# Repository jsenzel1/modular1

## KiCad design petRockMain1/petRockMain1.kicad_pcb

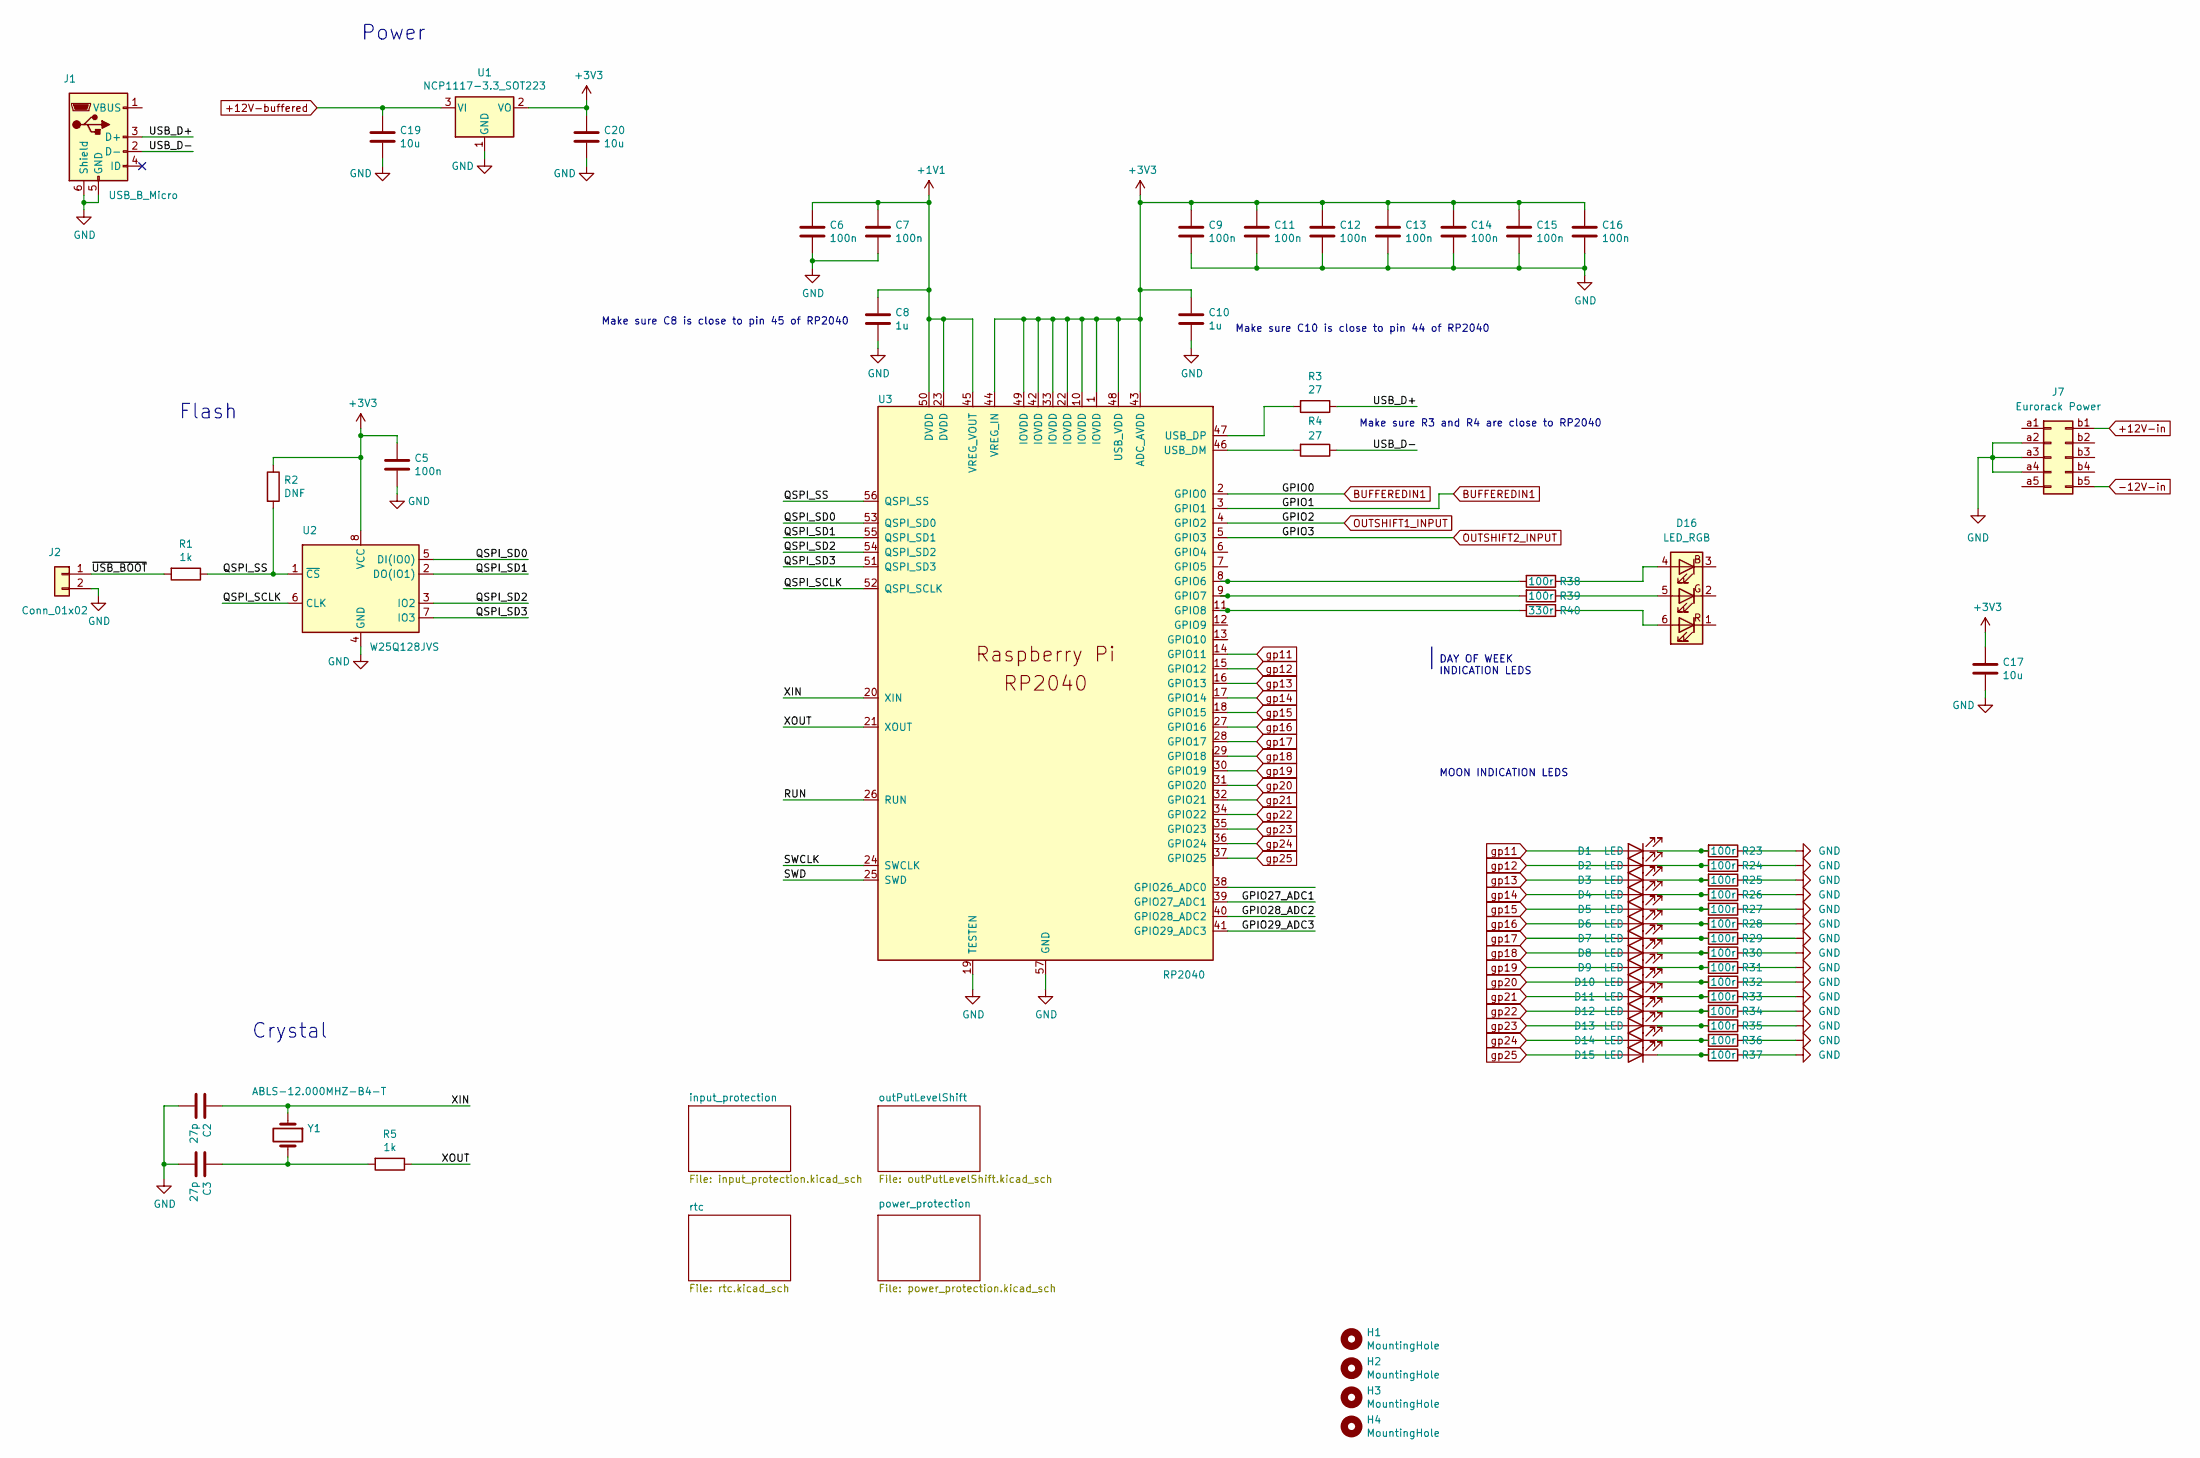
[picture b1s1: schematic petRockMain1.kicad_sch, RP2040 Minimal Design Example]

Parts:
C2, C3: 27p; C_0402_1005Metric
C5, C6, C7, C9, C11, C12, C13, C14, C15, C16: 100n; C_0402_1005Metric
C8, C10: 1u; C_0402_1005Metric
C17, C19, C20: 10u; C_0805_2012Metric
D1, D2, D3, D4, D5, D6, D7, D8, D9, D10, D11, D12, D13, D14, D15: LED; C_0603_1608Metric
D16: LED_RGB; LED_RGB_5050-6
H1, H2, H3, H4: MountingHole; MountingHole_2.7mm_M2.5
J1: USB_B_Micro; USB_Micro-B_Amphenol_10103594-0001LF_Horizontal_modified
J2: Conn_01x02; PinHeader_1x02_P2.54mm_Vertical
J7: Eurorack Power; PinHeader_2x05_P1.00mm_Vertical
R1, R5: 1k; C_0402_1005Metric
R2: DNF; C_0402_1005Metric
R3, R4: 27; C_0402_1005Metric
R23, R24, R25, R26, R27, R28, R29, R30, R31, R32, R33, R34, R35, R36, R37, R38, R39: 100r; C_0402_1005Metric
R40: 330r; C_0402_1005Metric
U1: NCP1117-3.3_SOT223; SOT-223-3_TabPin2
U2: W25Q128JVS; SOIC-8_5.23x5.23mm_P1.27mm
U3: RP2040; RP2040-QFN-56
Y1: ABLS-12.000MHZ-B4-T; Crystal_SMD_HC49-US

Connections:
+1V1: C6.1, C7.1, C8.1, U3.23 (DVDD), U3.45 (VREG_VOUT), U3.50 (DVDD)
+3V3: C5.1, C9.1, C10.1, C11.1, C12.1, C13.1, C14.1, C15.1, C16.1, C17.1, C20.1, R2.1, U1.2 (VO), U2.8 (VCC), U3.1 (IOVDD), U3.10 (IOVDD), U3.22 (IOVDD), U3.33 (IOVDD), U3.42 (IOVDD), U3.43 (ADC_AVDD), U3.44 (VREG_IN), U3.48 (USB_VDD), U3.49 (IOVDD); also elsewhere on the board
+12V-buffered: C19.1, U1.3 (VI); also elsewhere on the board
/GPIO27_ADC1: U3.39 (GPIO27_ADC1)
/GPIO28_ADC2: U3.40 (GPIO28_ADC2)
/GPIO29_ADC3: U3.41 (GPIO29_ADC3)
/QSPI_SCLK: U2.6 (CLK), U3.52 (QSPI_SCLK)
/QSPI_SD0: U2.5 (DI(IO0)), U3.53 (QSPI_SD0)
/QSPI_SD1: U2.2 (DO(IO1)), U3.55 (QSPI_SD1)
/QSPI_SD2: U2.3 (IO2), U3.54 (QSPI_SD2)
/QSPI_SD3: U2.7 (IO3), U3.51 (QSPI_SD3)
/QSPI_SS: R1.1, R2.2, U2.1 (~CS), U3.56 (QSPI_SS)
/RUN: U3.26 (RUN)
/SWCLK: U3.24 (SWCLK)
/SWD: U3.25 (SWD)
/USB_D+: J1.3 (D+), R3.1
/USB_D-: J1.2 (D-), R4.1
/XIN: C2.1, U3.20 (XIN), Y1.1
/XOUT: R5.1, U3.21 (XOUT)
/~USB_BOOT: J2.1, R1.2
BUFFEREDIN1: U3.2 (GPIO0), U3.3 (GPIO1); also elsewhere on the board
GND: C2.2, C3.2, C5.2, C6.2, C7.2, C8.2, C9.2, C10.2, C11.2, C12.2, C13.2, C14.2, C15.2, C16.2, C17.2, C19.2, C20.2, J1.5 (GND), J1.6 (Shield), J2.2, J7.a2, J7.a3, J7.a4, R23.1, R24.1, R25.1, R26.1, R27.1, R28.1, R29.1, R30.1, R31.1, R32.1, R33.1, R34.1, R35.1, R36.1, R37.1, U1.1 (GND), U2.4 (GND), U3.19 (TESTEN), U3.57 (GND); also elsewhere on the board
unnamed: C3.1, R5.2, Y1.2
unnamed: D1.1 (K), R23.2
unnamed: D2.1 (K), R24.2
unnamed: D3.1 (K), R25.2
unnamed: D4.1 (K), R26.2
unnamed: D5.1 (K), R27.2
unnamed: D6.1 (K), R28.2
unnamed: D7.1 (K), R29.2
unnamed: D8.1 (K), R30.2
unnamed: D9.1 (K), R31.2
unnamed: D10.1 (K), R32.2
unnamed: D11.1 (K), R33.2
unnamed: D12.1 (K), R34.2
unnamed: D13.1 (K), R35.2
unnamed: D14.1 (K), R36.2
unnamed: D15.1 (K), R37.2
unnamed: D16.4 (BA), R38.1
unnamed: D16.5 (GA), R39.1
unnamed: D16.6 (RA), R40.1
unnamed: R3.2, U3.47 (USB_DP)
unnamed: R4.2, U3.46 (USB_DM)
unnamed: R38.2, U3.8 (GPIO6)
unnamed: R39.2, U3.9 (GPIO7)
unnamed: R40.2, U3.11 (GPIO8)
OUTSHIFT1_INPUT: U3.4 (GPIO2); also elsewhere on the board
OUTSHIFT2_INPUT: U3.5 (GPIO3); also elsewhere on the board
gp11: D1.2 (A), U3.14 (GPIO11)
gp12: D2.2 (A), U3.15 (GPIO12)
gp13: D3.2 (A), U3.16 (GPIO13)
gp14: D4.2 (A), U3.17 (GPIO14)
gp15: D5.2 (A), U3.18 (GPIO15)
gp16: D6.2 (A), U3.27 (GPIO16)
gp17: D7.2 (A), U3.28 (GPIO17)
gp18: D8.2 (A), U3.29 (GPIO18)
gp19: D9.2 (A), U3.30 (GPIO19)
gp20: D10.2 (A), U3.31 (GPIO20)
gp21: D11.2 (A), U3.32 (GPIO21)
gp22: D12.2 (A), U3.34 (GPIO22)
gp23: D13.2 (A), U3.35 (GPIO23)
gp24: D14.2 (A), U3.36 (GPIO24)
gp25: D15.2 (A), U3.37 (GPIO25)

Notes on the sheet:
Power
Flash
Crystal
MOON INDICATION LEDS
Make sure R3 and R4 are close to RP2040
Make sure C8 is close to pin 45 of RP2040
DAY OF WEEK INDICATION LEDS
Make sure C10 is close to pin 44 of RP2040

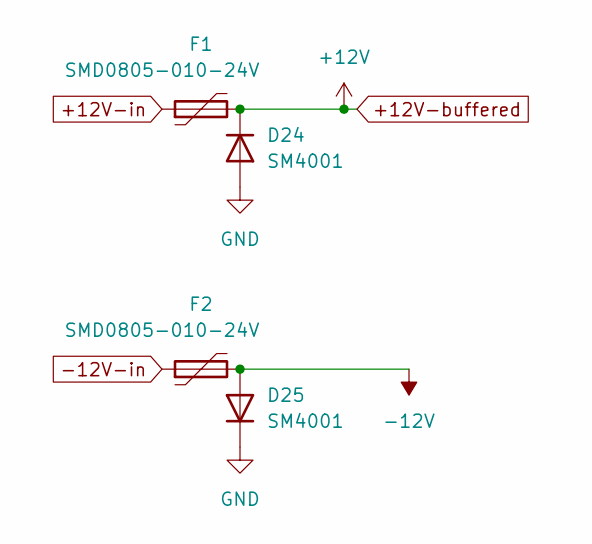
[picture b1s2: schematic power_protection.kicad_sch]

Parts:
D24, D25: SM4001; D_MELF
F1, F2: SMD0805-010-24V; Fuse_0805_2012Metric

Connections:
+12V-buffered: D24.1 (K), F1.2; also elsewhere on the board
+12V-in: F1.1
-12V: D25.2 (A), F2.2
-12V-in: F2.1
GND: D24.2 (A), D25.1 (K); also elsewhere on the board

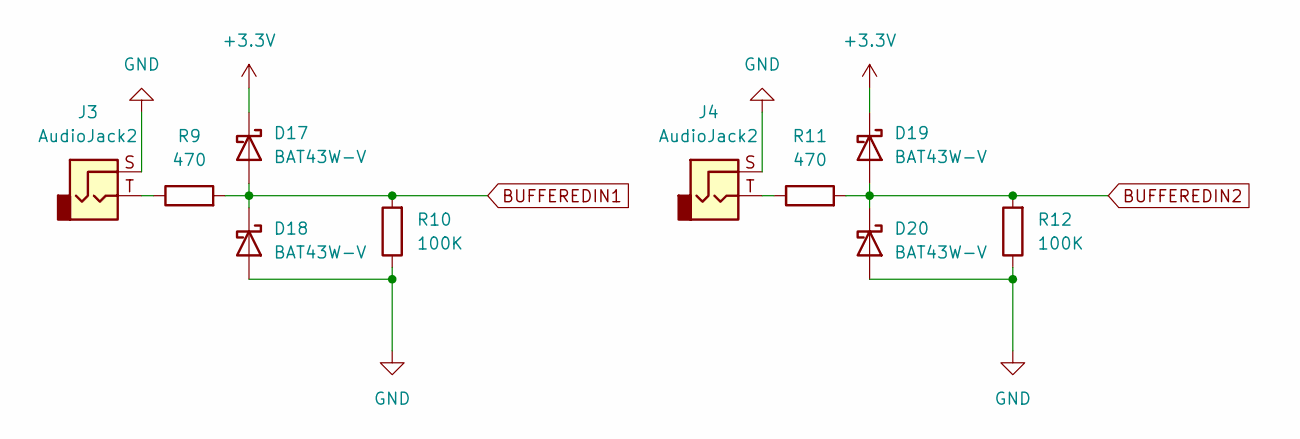
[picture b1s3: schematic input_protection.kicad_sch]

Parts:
D17, D18, D19, D20: BAT43W-V; D_SOD-123
J3, J4: AudioJack2; Jack_3.5mm_QingPu_WQP-PJ398SM_Vertical_CircularHoles
R9, R11: 470; C_0402_1005Metric
R10, R12: 100K; C_0402_1005Metric

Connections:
+3.3V: D17.1 (K), D19.1 (K)
BUFFEREDIN1: D17.2 (A), D18.1 (K), R9.2, R10.2; also elsewhere on the board
BUFFEREDIN2: D19.2 (A), D20.1 (K), R11.2, R12.2
GND: D18.2 (A), D20.2 (A), J3.S, J4.S, R10.1, R12.1; also elsewhere on the board
unnamed: J3.T, R9.1
unnamed: J4.T, R11.1

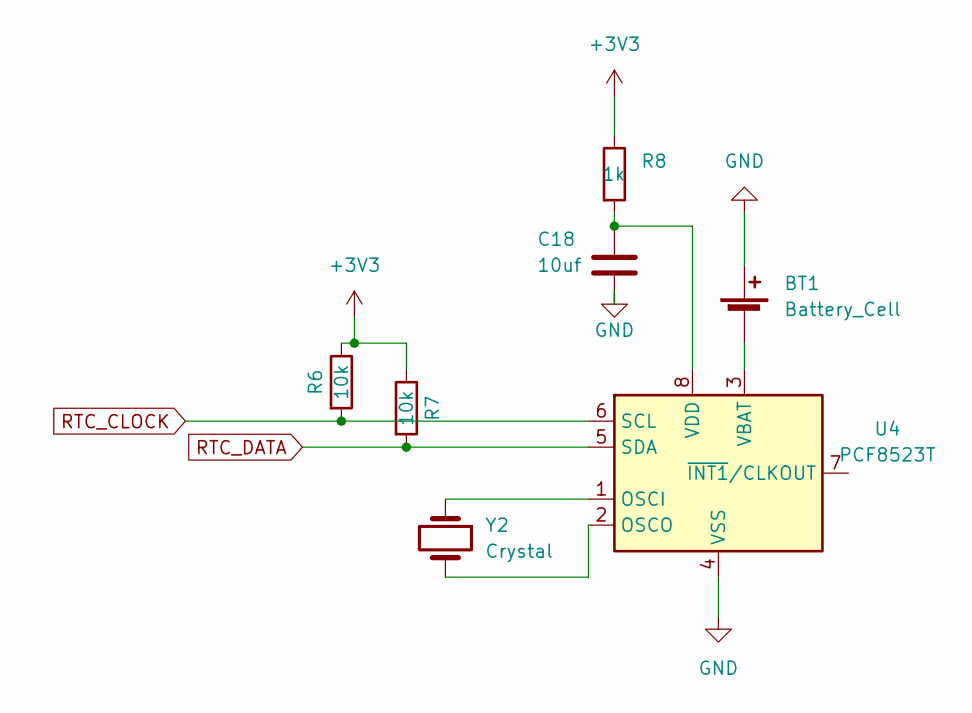
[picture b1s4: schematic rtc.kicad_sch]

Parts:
BT1: Battery_Cell; BatteryHolder_Keystone_500
C18: 10uf; C_0805_2012Metric
R6, R7: 10k; C_0402_1005Metric
R8: 1k; C_0402_1005Metric
U4: PCF8523T; SOIC-8_3.9x4.9mm_P1.27mm
Y2: Crystal; Crystal_SMD_3215-2Pin_3.2x1.5mm

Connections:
+3V3: R6.1, R7.1, R8.1; also elsewhere on the board
GND: BT1.1 (+), C18.2, U4.4 (VSS); also elsewhere on the board
unnamed: BT1.2 (-), U4.3 (VBAT)
unnamed: C18.1, R8.2, U4.8 (VDD)
unnamed: U4.1 (OSCI), Y2.1
unnamed: U4.2 (OSCO), Y2.2
RTC_CLOCK: R6.2, U4.6 (SCL)
RTC_DATA: R7.2, U4.5 (SDA)

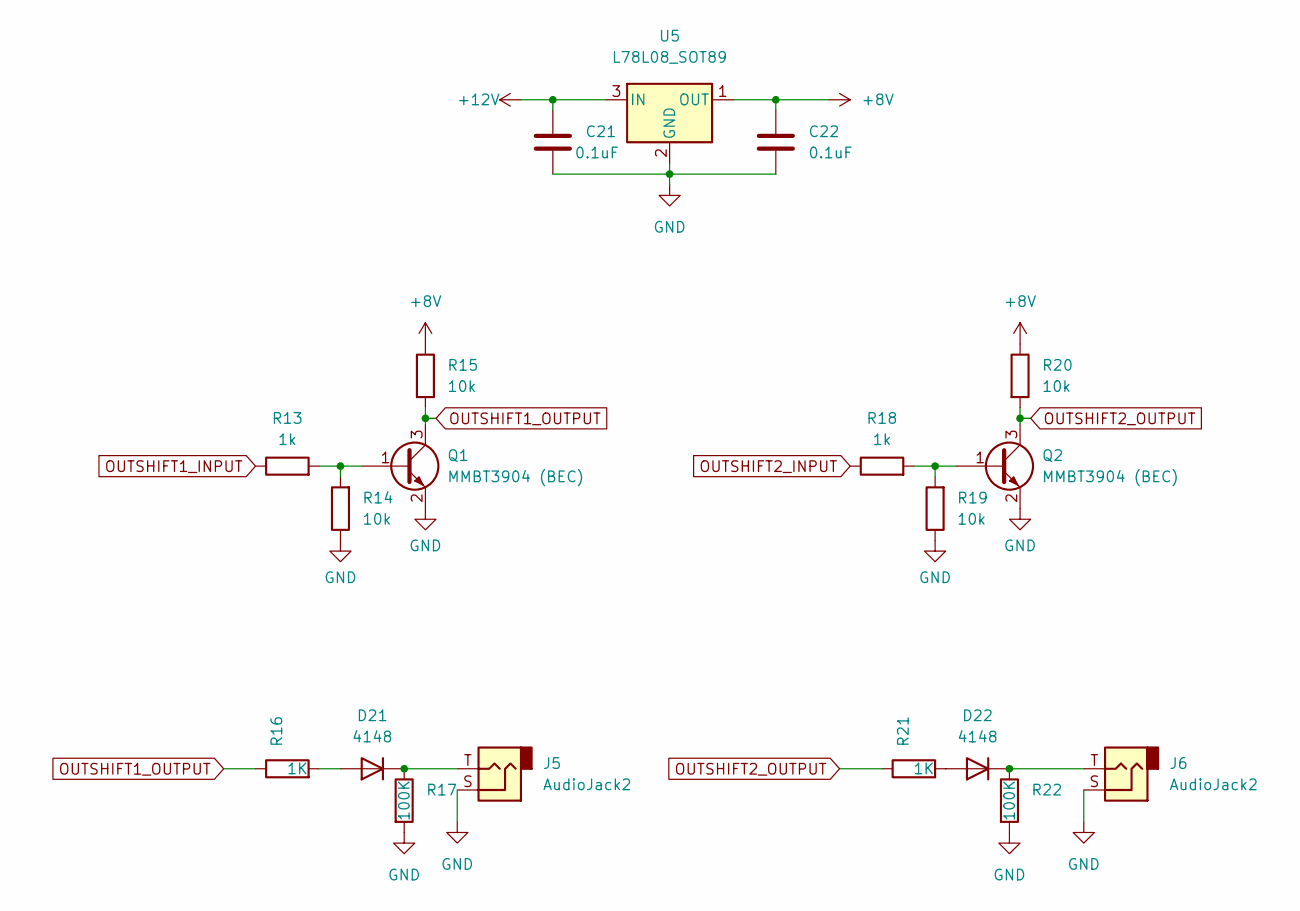
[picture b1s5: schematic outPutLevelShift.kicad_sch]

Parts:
C21, C22: 0.1uF; C_0402_1005Metric
D21, D22: 4148; D_SOD-123
J5, J6: AudioJack2; Jack_3.5mm_QingPu_WQP-PJ398SM_Vertical_CircularHoles
Q1, Q2: MMBT3904 (BEC); SOT-23
R13, R18: 1k; C_0402_1005Metric
R14, R15, R19, R20: 10k; C_0402_1005Metric
R16, R21: 1K; C_0402_1005Metric
R17, R22: 100K; C_0402_1005Metric
U5: L78L08_SOT89; SOT-89-3

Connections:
+8V: C22.1, R15.1, R20.1, U5.1 (OUT)
+12V-buffered: C21.1, U5.3 (IN); also elsewhere on the board
GND: C21.2, C22.2, J5.S, J6.S, Q1.2 (E), Q2.2 (E), R14.1, R17.2, R19.1, R22.2, U5.2 (GND); also elsewhere on the board
unnamed: D21.1 (K), J5.T, R17.1
unnamed: D21.2 (A), R16.2
unnamed: D22.1 (K), J6.T, R22.1
unnamed: D22.2 (A), R21.2
unnamed: Q1.1 (B), R13.2, R14.2
unnamed: Q2.1 (B), R18.2, R19.2
OUTSHIFT1_INPUT: R13.1; also elsewhere on the board
OUTSHIFT1_OUTPUT: Q1.3 (C), R15.2, R16.1
OUTSHIFT2_INPUT: R18.1; also elsewhere on the board
OUTSHIFT2_OUTPUT: Q2.3 (C), R20.2, R21.1

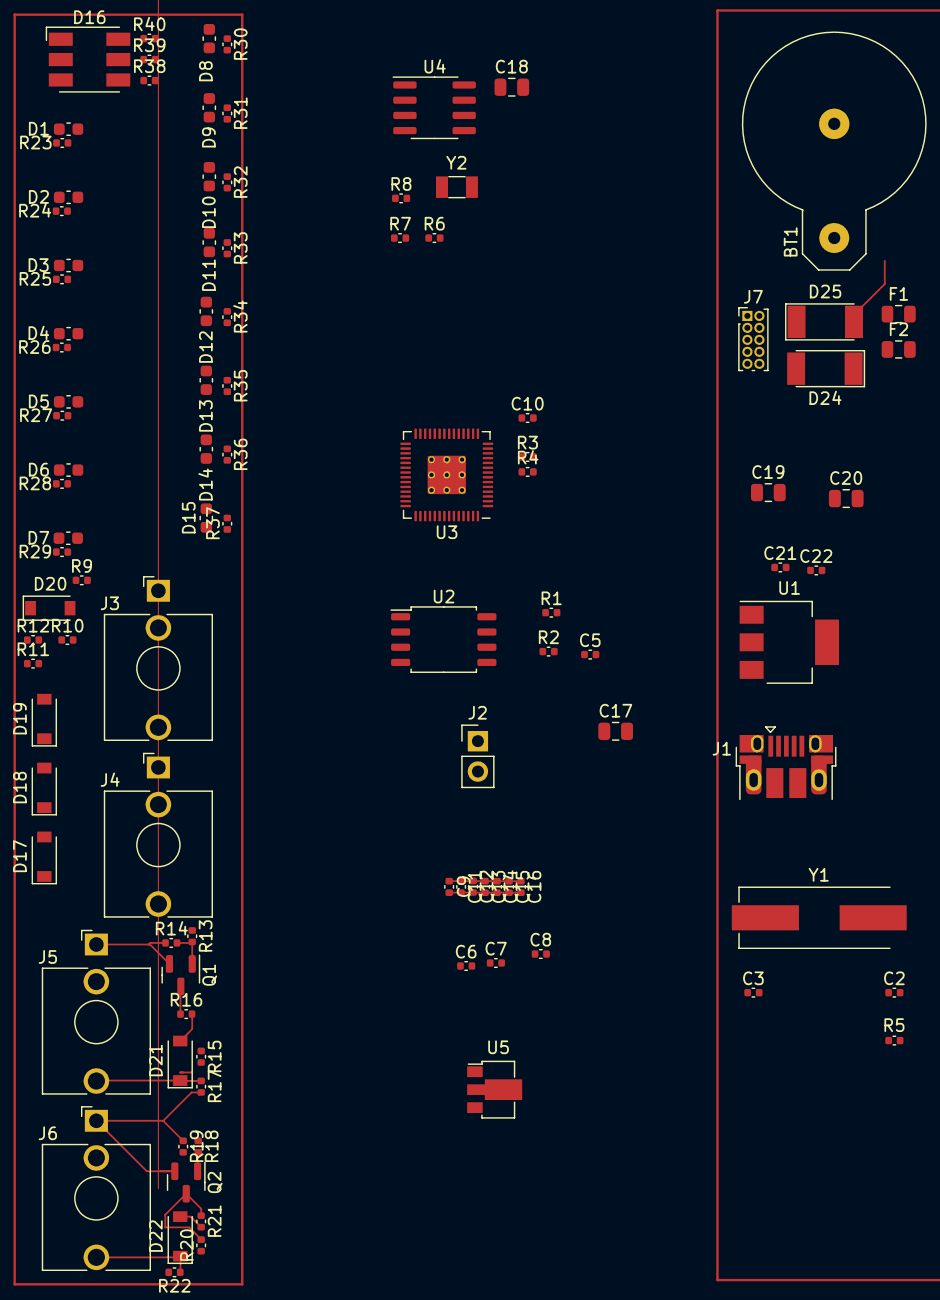
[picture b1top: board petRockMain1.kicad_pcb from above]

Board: 2 copper layers, 103 parts (0 on the bottom side), 77 nets.
